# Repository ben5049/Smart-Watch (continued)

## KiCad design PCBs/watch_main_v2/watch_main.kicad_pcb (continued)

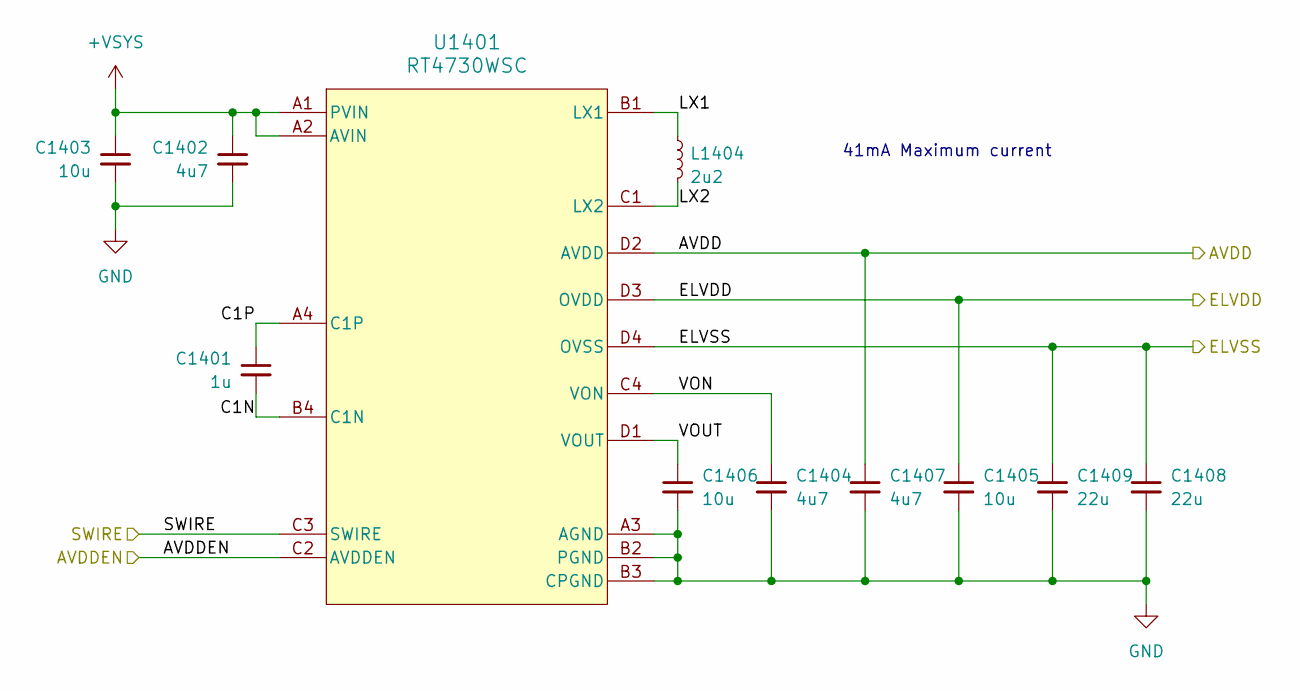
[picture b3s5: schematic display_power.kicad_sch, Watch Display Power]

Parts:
C1401: 1u; C_0402_1005Metric
C1402, C1404, C1407: 4u7; C_0402_1005Metric
C1403, C1405, C1406: 10u; C_0402_1005Metric
C1408, C1409: 22u; C_0402_1005Metric
L1404: 2u2; L_Murata_DFE201610P
U1401: RT4730WSC

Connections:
+VSYS: C1402.1, C1403.1, U1401.A1 (PVIN), U1401.A2 (AVIN); also elsewhere on the board
/Display Connector/AVDD: C1407.1, U1401.D2 (AVDD); also elsewhere on the board
/Display Connector/ELVDD: C1405.1, U1401.D3 (OVDD); also elsewhere on the board
/Display Connector/SWIRE: U1401.C3 (SWIRE); also elsewhere on the board
/Display Power/AVDDEN: U1401.C2 (AVDDEN); also elsewhere on the board
/Display Power/C1N: C1401.2, U1401.B4 (C1N)
/Display Power/C1P: C1401.1, U1401.A4 (C1P)
/Display Power/ELVSS: C1408.1, C1409.1, U1401.D4 (OVSS); also elsewhere on the board
/Display Power/LX1: L1404.1, U1401.B1 (LX1)
/Display Power/LX2: L1404.2, U1401.C1 (LX2)
/Display Power/VON: C1404.1, U1401.C4 (VON)
/Display Power/VOUT: C1406.1, U1401.D1 (VOUT)
GND: C1402.2, C1403.2, C1404.2, C1405.2, C1406.2, C1407.2, C1408.2, C1409.2, U1401.A3 (AGND), U1401.B2 (PGND), U1401.B3 (CPGND); also elsewhere on the board

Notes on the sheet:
41mA Maximum current

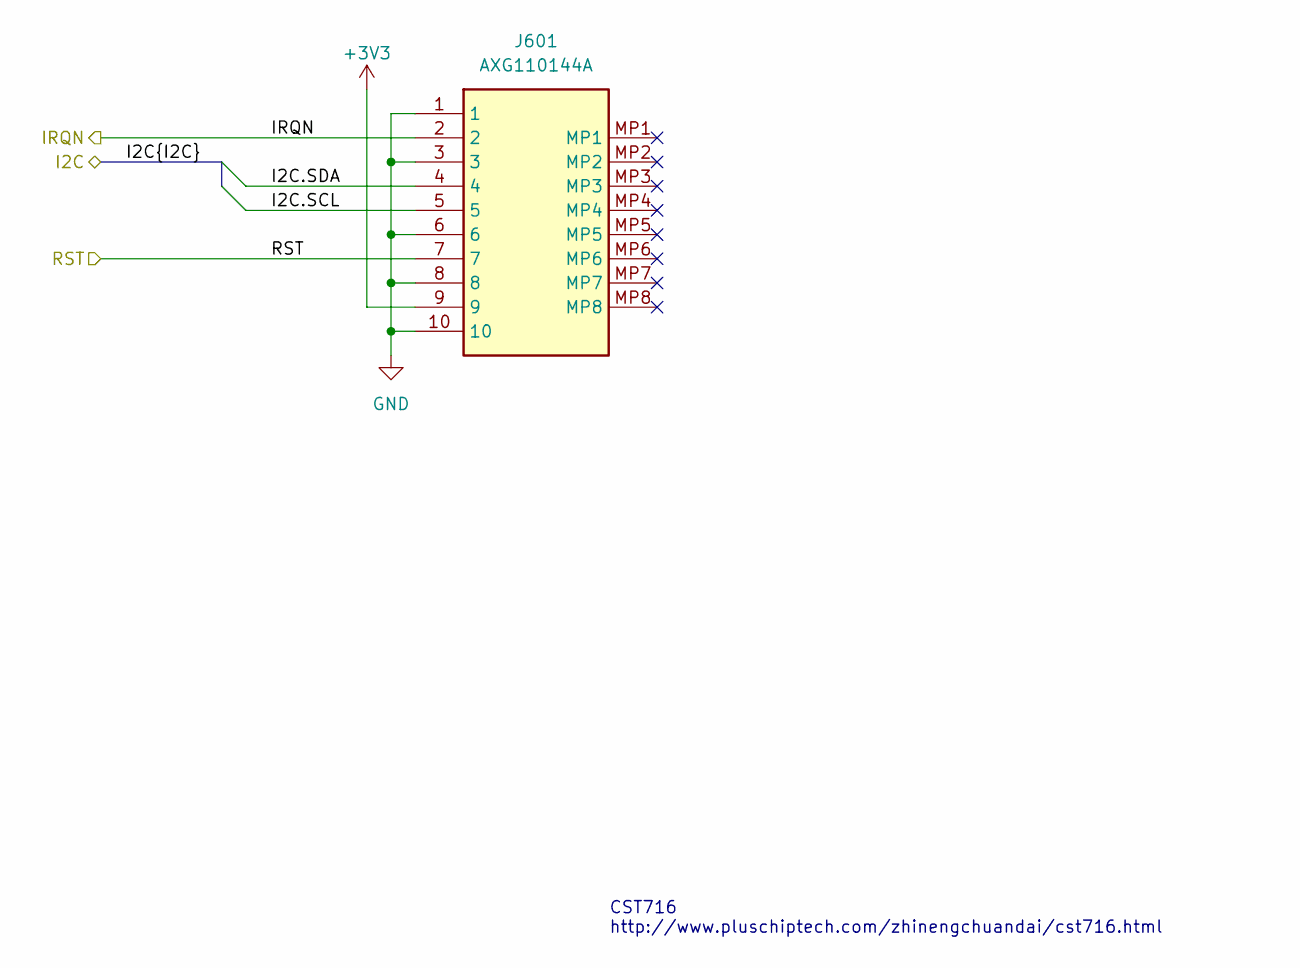
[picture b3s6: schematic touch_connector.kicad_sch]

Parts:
J601: AXG110144A; Mouser Part Number N/A

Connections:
+3V3: J601.9; also elsewhere on the board
/I2C1.SCL: J601.5; also elsewhere on the board
/I2C1.SDA: J601.4; also elsewhere on the board
/STM32/TOUCH_INT: J601.2; also elsewhere on the board
/STM32/TOUCH_RST: J601.7; also elsewhere on the board
GND: J601.1, J601.3, J601.6, J601.8, J601.10; also elsewhere on the board

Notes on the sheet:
CST716 http://www.pluschiptech.com/zhinengchuandai/cst716.html

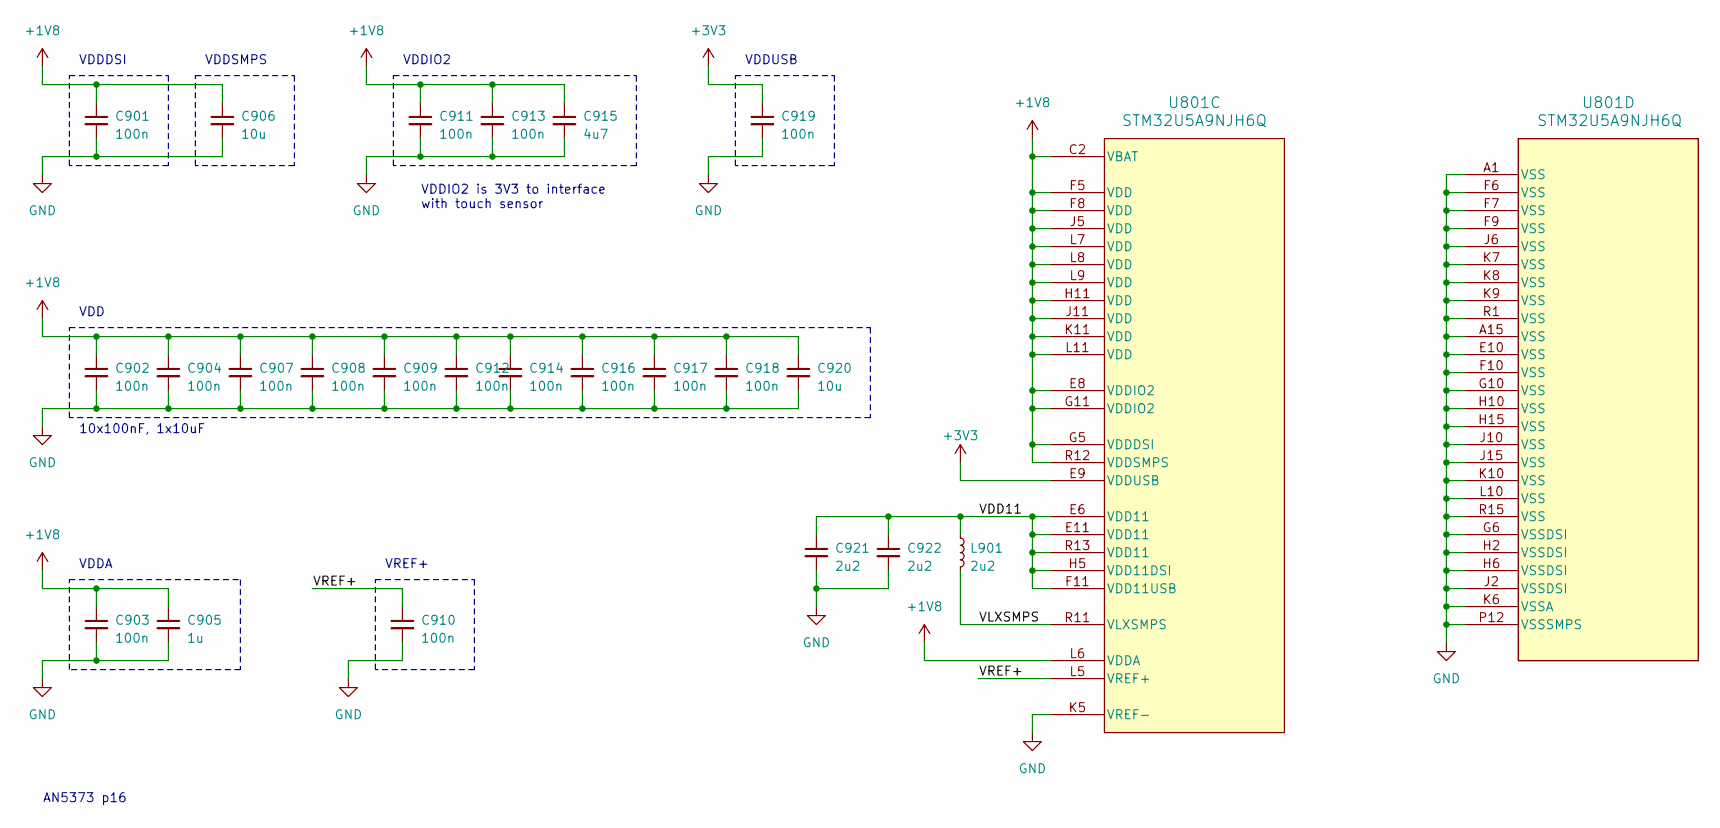
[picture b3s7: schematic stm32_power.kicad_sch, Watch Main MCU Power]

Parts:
C901, C902, C903, C904, C907, C908, C909, C910, C911, C912, C913, C914, C916, C917, C918, C919: 100n; C_0402_1005Metric
C905: 1u; C_0402_1005Metric
C906, C920: 10u; C_0402_1005Metric
C915: 4u7; C_0402_1005Metric
C921, C922: 2u2; C_0402_1005Metric
L901: 2u2; L_Murata_DFE201610P
U801: STM32U5A9NJH6Q; TFBGA216_13X13_STM

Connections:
+1V8: C901.1, C902.1, C903.1, C904.1, C905.1, C906.1, C907.1, C908.1, C909.1, C911.1, C912.1, C913.1, C914.1, C915.1, C916.1, C917.1, C918.1, C920.1, U801.C2 (VBAT), U801.E8 (VDDIO2), U801.F5 (VDD), U801.F8 (VDD), U801.G5 (VDDDSI), U801.G11 (VDDIO2), U801.H11 (VDD), U801.J5 (VDD), U801.J11 (VDD), U801.K11 (VDD), U801.L6 (VDDA), U801.L7 (VDD), U801.L8 (VDD), U801.L9 (VDD), U801.L11 (VDD), U801.R12 (VDDSMPS); also elsewhere on the board
+3V3: C919.1, U801.E9 (VDDUSB); also elsewhere on the board
/STM32 Power/VDD11: C921.1, C922.1, L901.1, U801.E6 (VDD11), U801.E11 (VDD11), U801.F11 (VDD11USB), U801.H5 (VDD11DSI), U801.R13 (VDD11)
/STM32 Power/VLXSMPS: L901.2, U801.R11 (VLXSMPS)
/STM32 Power/VREF+: C910.1, U801.L5 (VREF+)
GND: C901.2, C902.2, C903.2, C904.2, C905.2, C906.2, C907.2, C908.2, C909.2, C910.2, C911.2, C912.2, C913.2, C914.2, C915.2, C916.2, C917.2, C918.2, C919.2, C920.2, C921.2, C922.2, U801.A1 (VSS), U801.A15 (VSS), U801.E10 (VSS), U801.F6 (VSS), U801.F7 (VSS), U801.F9 (VSS), U801.F10 (VSS), U801.G6 (VSSDSI), U801.G10 (VSS), U801.H2 (VSSDSI), U801.H6 (VSSDSI), U801.H10 (VSS), U801.H15 (VSS), U801.J2 (VSSDSI), U801.J6 (VSS), U801.J10 (VSS), U801.J15 (VSS), U801.K5 (VREF-), U801.K6 (VSSA), U801.K7 (VSS), U801.K8 (VSS), U801.K9 (VSS), U801.K10 (VSS), U801.L10 (VSS), U801.P12 (VSSSMPS), U801.R1 (VSS), U801.R15 (VSS); also elsewhere on the board

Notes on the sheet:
VDDIO2 is 3V3 to interface with touch sensor
VDDUSB
VDDIO2
VREF+
VDD
VDDSMPS
VDDA
AN5373 p16
10x100nF, 1x10uF
VDDDSI

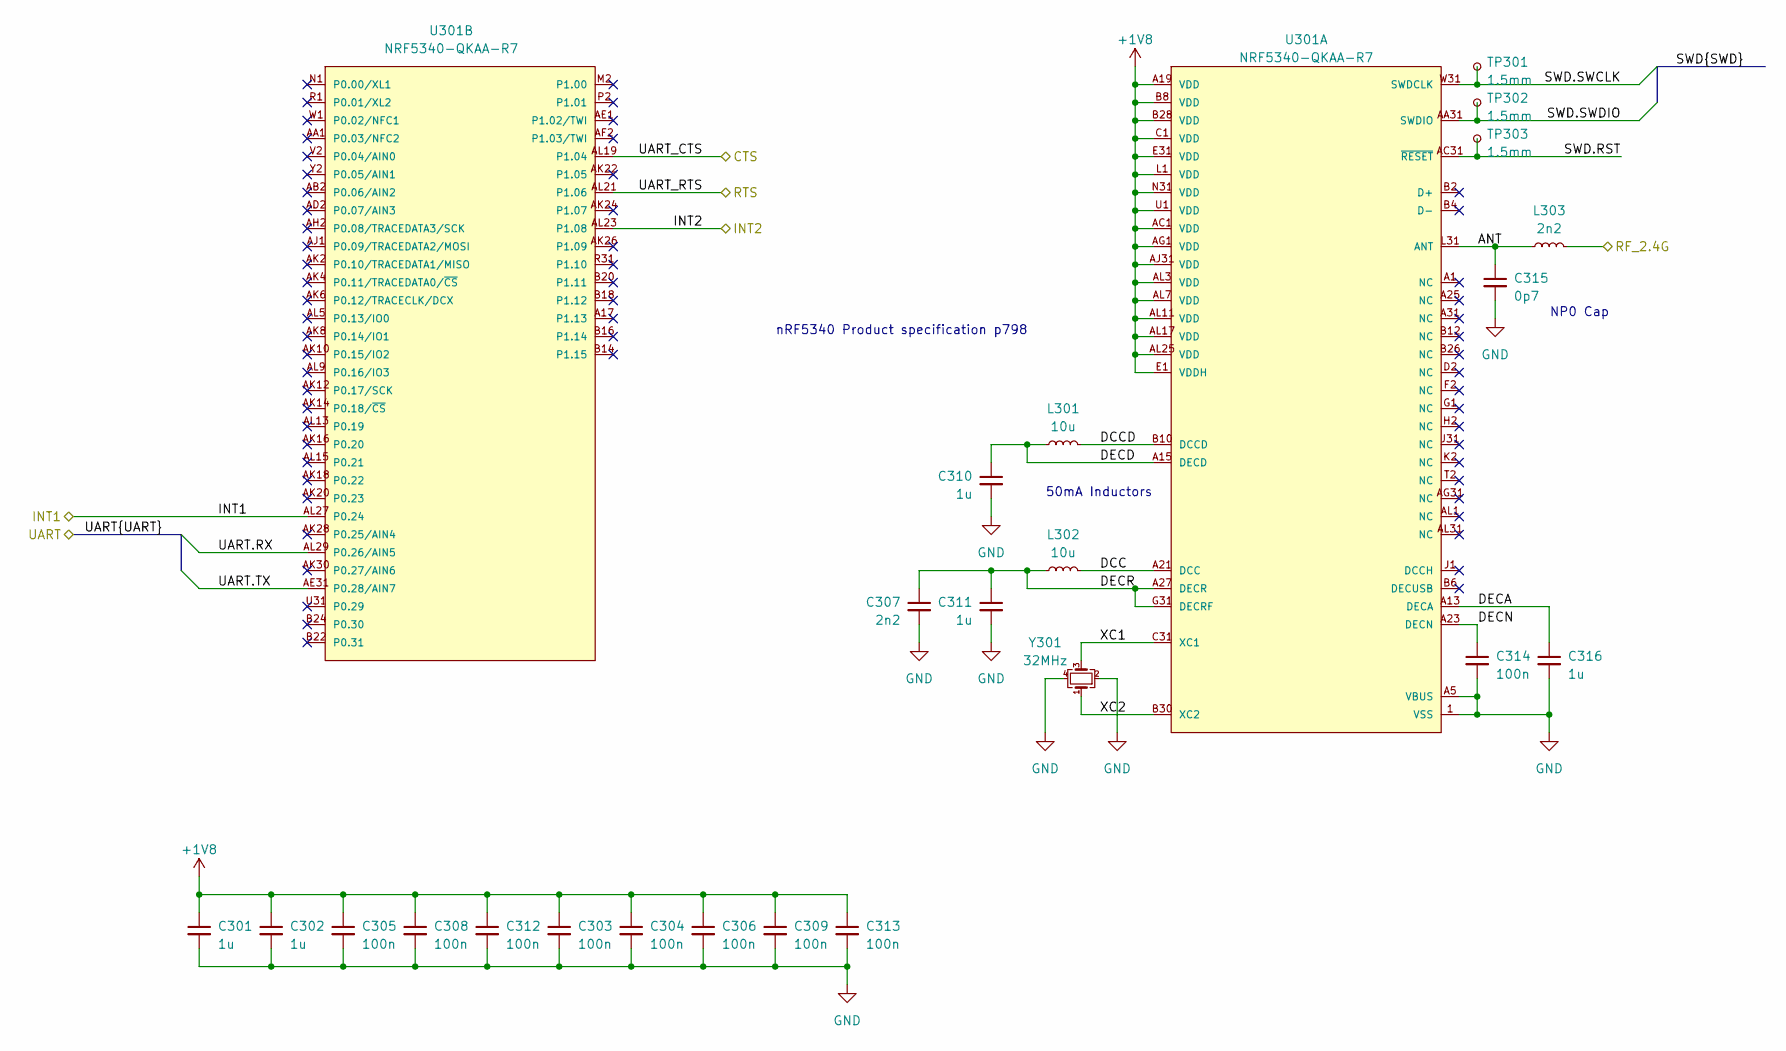
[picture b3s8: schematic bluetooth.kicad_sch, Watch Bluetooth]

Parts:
C301, C302, C310, C311, C316: 1u; C_0402_1005Metric
C303, C304, C305, C306, C308, C309, C312, C313, C314: 100n; C_0402_1005Metric
C307: 2n2; C_0402_1005Metric
C315: 0p7; C_0402_1005Metric
L301, L302: 10u; L_TDK_MLZ1608
L303: 2n2; L_0402_1005Metric
TP301, TP302, TP303: 1.5mm; TestPoint_Pad_D1.5mm
U301: NRF5340-QKAA-R7; NRF5340-QKAA-R7_modified; mouser part number 949-NRF5340-QKAA-R7; digikey description BLE 5.2 SOC
Y301: 32MHz; Crystal_SMD_2016-4Pin_2.0x1.6mm

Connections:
+1V8: C301.1, C302.1, C303.1, C304.1, C305.1, C306.1, C308.1, C309.1, C312.1, C313.1, U301.A19 (VDD), U301.AC1 (VDD), U301.AG1 (VDD), U301.AJ31 (VDD), U301.AL3 (VDD), U301.AL7 (VDD), U301.AL11 (VDD), U301.AL17 (VDD), U301.AL25 (VDD), U301.B8 (VDD), U301.B28 (VDD), U301.C1 (VDD), U301.E1 (VDDH), U301.E31 (VDD), U301.L1 (VDD), U301.N31 (VDD), U301.U1 (VDD); also elsewhere on the board
/Antenna/RF_2.4G: L303.2; also elsewhere on the board
/Bluetooth/ANT: C315.1, L303.1, U301.L31 (ANT)
/Bluetooth/DCC: L302.2, U301.A21 (DCC)
/Bluetooth/DCCD: L301.2, U301.B10 (DCCD)
/Bluetooth/DECA: C316.1, U301.A13 (DECA)
/Bluetooth/DECD: C310.1, L301.1, U301.A15 (DECD)
/Bluetooth/DECN: C314.1, U301.A23 (DECN)
/Bluetooth/DECR: C307.1, C311.1, L302.1, U301.A27 (DECR), U301.G31 (DECRF)
/Bluetooth/INT1: U301.AL27 (P0.24); also elsewhere on the board
/Bluetooth/INT2: U301.AL23 (P1.08); also elsewhere on the board
/Bluetooth/SWD.RST: TP303.1, U301.AC31 (~RESET)
/Bluetooth/SWD.SWCLK: TP301.1, U301.W31 (SWDCLK)
/Bluetooth/SWD.SWDIO: TP302.1, U301.AA31 (SWDIO)
/Bluetooth/UART_CTS: U301.AL19 (P1.04); also elsewhere on the board
/Bluetooth/UART_RTS: U301.AL21 (P1.06); also elsewhere on the board
/Bluetooth/XC1: U301.C31 (XC1), Y301.3
/Bluetooth/XC2: U301.B30 (XC2), Y301.1
/LPUART1.RX: U301.AL29 (P0.26/AIN5); also elsewhere on the board
/LPUART1.TX: U301.AE31 (P0.28/AIN7); also elsewhere on the board
GND: C301.2, C302.2, C303.2, C304.2, C305.2, C306.2, C307.2, C308.2, C309.2, C310.2, C311.2, C312.2, C313.2, C314.2, C315.2, C316.2, U301.1 (VSS), U301.A5 (VBUS), Y301.2, Y301.4; also elsewhere on the board

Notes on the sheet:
nRF5340 Product specification p798
NP0 Cap
50mA Inductors

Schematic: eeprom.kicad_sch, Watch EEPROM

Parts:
IC1801: M24256X-FCU6T_VF; BGA4C50P2X2_70X98X33; Mouser Part Number 511-M24256X-FCU6T/VF

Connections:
+1V8: IC1801.A1 (VCC); also elsewhere on the board
/I2C4.SCL: IC1801.A2 (SCL); also elsewhere on the board
/I2C4.SDA: IC1801.B1 (SDA); also elsewhere on the board
GND: IC1801.B2 (VSS); also elsewhere on the board

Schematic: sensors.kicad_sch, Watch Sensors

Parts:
C1301: 220n; C_0402_1005Metric
C1302, C1304, C1305, C1306, C1307: 100n; C_0402_1005Metric
C1303: 10u; C_0402_1005Metric
IC1301: IIS2MDCTR; Mouser Part Number 511-IIS2MDCTR
IC1302: OPT3004DNPR; SON65P200X200X65-7N-D; Mouser Part Number 595-OPT3004DNPR
U1301: LSM6DSO16IS; LGA14_LSM6_STM

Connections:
+1V8: C1302.1, C1303.1, C1304.1, C1305.1, C1306.1, C1307.1, IC1301.9 (VDD), IC1301.10 (VDD_IO), IC1302.1 (VDD), U1301.2 (MSDA), U1301.3 (MSCL), U1301.5 (VDD_IO), U1301.8 (VDD); also elsewhere on the board
/I2C3.SCL: IC1301.1 (SCL/SPC), IC1302.4 (SCL); also elsewhere on the board
/I2C3.SDA: IC1301.4 (SDA/SDI/SDO), IC1302.6 (SDA); also elsewhere on the board
/SPI1.CS: U1301.12 (CS); also elsewhere on the board
/SPI1.MISO: U1301.1 (SDO/SA0); also elsewhere on the board
/SPI1.MOSI: U1301.14 (SDA); also elsewhere on the board
/SPI1.SCK: U1301.13 (SCL); also elsewhere on the board
/STM32/ALS_INT: IC1302.5 (INT); also elsewhere on the board
/STM32/IMU_INT1: U1301.4 (INT1); also elsewhere on the board
/STM32/IMU_INT2: U1301.9 (INT2); also elsewhere on the board
/STM32/MAG_INT: IC1301.7 (INT/DRDY); also elsewhere on the board
/Sensors/C1: C1301.1, IC1301.5 (C1)
GND: C1301.2, C1302.2, C1303.2, C1304.2, C1305.2, C1306.2, C1307.2, IC1301.6 (GND_1), IC1301.8 (GND_2), IC1302.2 (ADDR), IC1302.3 (GND), IC1302.7 (EP), U1301.6 (GND), U1301.7 (GND); also elsewhere on the board

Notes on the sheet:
Address = 0x1E
Address = 0x6A (SA0=0)
Address = 0x44 (ADDR=0)
Typical application: LSM6DSO16IS datasheet p25
Typical application: IIS2MDCTR datasheet p19
Typical application: OPT3004 datasheet p19

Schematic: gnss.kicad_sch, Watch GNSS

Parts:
C401: 10n; C_0402_1005Metric
C402: 120p; C_0402_1005Metric
C403: 100n; C_0402_1005Metric
FL401: B39162B4327P810; mouser part number 871-B39162B4327P810; digikey description FILTER SAW 5SMD
IC401: BGA725L6E6327FTSA1; BGS12SN6E6327XTSA1; Mouser Part Number 726-BGA725L6E6327FTS
L401: 7n5; L_0402_1005Metric
R401: 10k; R_0402_1005Metric
U401: TESEO-LIV3FL; TESEOLIV3FL; Mouser Part Number 511-TESEO-LIV4FTR

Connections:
+1V8: C403.1, U401.6 (VBAT), U401.7 (VCCIO), U401.8 (VCC); also elsewhere on the board
/GNSS/ANT_OFF: IC401.6 (PON), R401.1, U401.13 (ANT_OFF)
/GNSS/LNA_IN: IC401.5 (AI), L401.2
/GNSS/LNA_OUT: FL401.1 (IN), IC401.3 (AO)
/GNSS/PPS: U401.4 (PPS); also elsewhere on the board
/GNSS/RF_1.575G: L401.1; also elsewhere on the board
/GNSS/RF_IN: C402.2, U401.11 (RF_IN)
/GNSS/RST: U401.9 (NRESET); also elsewhere on the board
/GNSS/SAW_OUT: C402.1, FL401.4 (OUT)
/GNSS/VCC_RF: C401.1, IC401.2 (VCC), U401.14 (VCC_RF)
/GNSS/WAKEUP: U401.5 (WAKEUP); also elsewhere on the board
/USART1.RX: U401.2 (UART-TX); also elsewhere on the board
/USART1.TX: U401.3 (UART-RX); also elsewhere on the board
GND: C401.2, C403.2, FL401.2 (GND_1), FL401.3 (GND_2), FL401.5 (GND_3), IC401.1 (GND), IC401.4 (GNDRF), R401.2, U401.1 (GND), U401.10 (GND_RF_1), U401.12 (GND_RF_2); also elsewhere on the board

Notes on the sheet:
UM2980 p12

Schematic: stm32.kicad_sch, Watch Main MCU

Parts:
C801, C802, C803, C804: 6p; C_0402_1005Metric
R801, R802, R803, R804, R805, R806, R807, R808, R809, R810: 4k7; R_0402_1005Metric
TP801, TP804, TP805, TP806, TP807: 1.5mm; TestPoint_Pad_D1.5mm
U801: STM32U5A9NJH6Q; TFBGA216_13X13_STM
Y801: 16MHz; Crystal_SMD_2016-4Pin_2.0x1.6mm
Y802: 32.768kHz; Crystal_SMD_2012-2Pin_2.0x1.2mm

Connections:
+1V8: R801.1, R802.1, R803.1, R804.1, R805.1, R806.1, R809.1, R810.1; also elsewhere on the board
+3V3: R807.1, R808.1; also elsewhere on the board
/Bluetooth/INT1: U801.C15 (PC6); also elsewhere on the board
/Bluetooth/INT2: U801.B15 (PC7); also elsewhere on the board
/Bluetooth/UART_CTS: U801.M6 (PB1); also elsewhere on the board
/Bluetooth/UART_RTS: U801.E14 (PG5); also elsewhere on the board
/DSI.CKN: U801.J1 (DSI_CKN); also elsewhere on the board
/DSI.CKP: U801.H1 (DSI_CKP); also elsewhere on the board
/DSI.D0N: U801.G2 (DSI_D0N); also elsewhere on the board
/DSI.D0P: U801.G1 (DSI_D0P); also elsewhere on the board
/Display Connector/DSI_TE: U801.L1 (PF10); also elsewhere on the board
/Display Connector/RESET: U801.L3 (PF7); also elsewhere on the board
/Display Connector/SWIRE: U801.A6 (PG12), U801.B7 (PG10); also elsewhere on the board
/Display Connector/TP_INT: U801.F2 (PJ8); also elsewhere on the board
/Display Connector/TP_RST: U801.E1 (PJ7); also elsewhere on the board
/Display Power/AVDDEN: U801.A7 (PG9); also elsewhere on the board
/Expansion Connector/GPIO1: U801.D9 (PD0); also elsewhere on the board
/Expansion Connector/GPIO2: U801.C9 (PD1); also elsewhere on the board
/Flash/CS2: U801.N4 (PA0); also elsewhere on the board
/Flash/INT: U801.F15 (PI13); also elsewhere on the board
/Flash/RST: U801.F14 (PI14); also elsewhere on the board
/Flash/RSTO: U801.G15 (PI10); also elsewhere on the board
/GNSS/PPS: U801.D12 (PA10); also elsewhere on the board
/GNSS/RST: U801.D1 (PJ3); also elsewhere on the board
/GNSS/WAKEUP: U801.E2 (PJ6); also elsewhere on the board
/I2C1.SCL: R807.2, U801.D7 (PG14); also elsewhere on the board
/I2C1.SDA: R808.2, U801.B6 (PG13); also elsewhere on the board
/I2C2.SCL: R801.2, U801.M12 (PB13); also elsewhere on the board
/I2C2.SDA: R802.2, U801.P13 (PB14); also elsewhere on the board
/I2C3.SCL: R803.2, U801.P2 (PC0); also elsewhere on the board
/I2C3.SDA: R804.2, U801.M1 (PC1); also elsewhere on the board
/I2C4.SCL: R805.2, U801.M13 (PD12); also elsewhere on the board
/I2C4.SDA: R806.2, U801.N14 (PD13); also elsewhere on the board
/I2C6.SCL: R809.2, U801.F1 (PJ10); also elsewhere on the board
/I2C6.SDA: R810.2, U801.H3 (PF0); also elsewhere on the board
/LPUART1.RX: U801.E13 (PG8); also elsewhere on the board
/LPUART1.TX: U801.D13 (PG7); also elsewhere on the board
/Micro SD/CD: U801.A9 (PD3); also elsewhere on the board
/Micro SD/EN: U801.A8 (PD4); also elsewhere on the board
/Microphone/CLOCK: U801.P9 (PE9); also elsewhere on the board
/Microphone/DATA: U801.P10 (PE10); also elsewhere on the board
/OSPI1.CLKN: U801.M11 (PB12); also elsewhere on the board
/OSPI1.CLKP: U801.N12 (PB10); also elsewhere on the board
/OSPI1.CS: U801.P11 (PE11); also elsewhere on the board
/OSPI1.DQS: U801.D14 (PG6); also elsewhere on the board
/OSPI1.IO0: U801.J14 (PI3); also elsewhere on the board
/OSPI1.IO1: U801.J13 (PI2); also elsewhere on the board
/OSPI1.IO2: U801.J12 (PI1); also elsewhere on the board
/OSPI1.IO3: U801.D10 (PH8); also elsewhere on the board
/OSPI1.IO4: U801.M14 (PH9); also elsewhere on the board
/OSPI1.IO5: U801.L13 (PH10); also elsewhere on the board
/OSPI1.IO6: U801.L14 (PH11); also elsewhere on the board
/OSPI1.IO7: U801.M15 (PH12); also elsewhere on the board
/Power/ENCHG: U801.R14 (PB15); also elsewhere on the board
/Power/INT: U801.P14 (PD10); also elsewhere on the board
/SDMMC1.CK: U801.C10 (PC12); also elsewhere on the board
/SDMMC1.CKIN: U801.C6 (PB8); also elsewhere on the board
/SDMMC1.CMD: U801.B9 (PD2); also elsewhere on the board
/SDMMC1.D0: U801.A14 (PC8); also elsewhere on the board
/SDMMC1.D1: U801.C14 (PC9); also elsewhere on the board
/SDMMC1.D2: U801.A10 (PC10); also elsewhere on the board
/SDMMC1.D3: U801.B10 (PC11); also elsewhere on the board
/SPI1.CS: U801.N6 (PB0); also elsewhere on the board
/SPI1.MISO: U801.P5 (PA6); also elsewhere on the board
/SPI1.MOSI: U801.R5 (PA7); also elsewhere on the board
/SPI1.SCK: U801.R4 (PA5); also elsewhere on the board
/STM32/ALS_INT: U801.M2 (PF6); also elsewhere on the board
/STM32/BTN: U801.M8 (PE8); also elsewhere on the board
/STM32/GPIO3: TP801.1, U801.B5
/STM32/HR_INT: U801.N15 (PD14); also elsewhere on the board
/STM32/IMU_INT1: U801.R7 (PB2); also elsewhere on the board
/STM32/IMU_INT2: U801.R8 (PF14); also elsewhere on the board
/STM32/LRA_EN: U801.P15 (PD9); also elsewhere on the board
/STM32/MAG_INT: U801.R6 (PC4); also elsewhere on the board
/STM32/OSC32_IN: C803.2, U801.B1 (PC14-OSC32_IN), Y802.2
/STM32/OSC32_OUT: C804.2, U801.C1 (PC15-OSC32_OUT), Y802.1
/STM32/OSC_IN: C801.2, U801.N1 (PH0-OSC_IN), Y801.3
/STM32/OSC_OUT: C802.2, U801.N2 (PH1-OSC_OUT), Y801.1
/STM32/SWD.RST: TP807.1, U801.R2 (NRST)
/STM32/SWD.SWCLK: TP806.1, U801.A12 (PA14)
/STM32/SWD.SWDIO: TP805.1, U801.C13 (PA13)
/STM32/SWO: TP804.1, U801.E7 (PB3)
/STM32/TOUCH_INT: U801.N9 (PE7); also elsewhere on the board
/STM32/TOUCH_RST: U801.N11 (PE12); also elsewhere on the board
/USART1.RX: U801.A3 (PB7); also elsewhere on the board
/USART1.TX: U801.A4 (PB6); also elsewhere on the board
/USART6.RX: U801.P1 (PC2); also elsewhere on the board
/USART6.TX: U801.N3 (PC3); also elsewhere on the board
/USB.DN: U801.B14 (PA11); also elsewhere on the board
/USB.DP: U801.B13 (PA12); also elsewhere on the board
GND: C801.1, C802.1, C803.1, C804.1, U801.B4 (PH3-BOOT0), Y801.2, Y801.4; also elsewhere on the board

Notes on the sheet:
CL = 8pF CS = 5pF ∴ CLx = 6pF
CL = 7pF CS = 4pF ∴ CLx = 6pF

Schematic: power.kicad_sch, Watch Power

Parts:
C201: 2u2; C_0402_1005Metric
C202: 1u; C_0402_1005Metric
C203, C204, C205, C206, C207, C208: 10u; C_0402_1005Metric
IC201: ADP5360ACBZ-2-R7; ADP5360ACBZ1R7; Mouser Part Number 584-ADP5360ACBZ-2-R7
L201, L202: 4u7; L_Murata_DFE201610P
Q201: DMP2104LP-7; DMP2104LP7; Mouser Part Number 621-DMP2104LP-7
R201: 10k; R_0402_1005Metric
R202: 100k; R_0402_1005Metric
TP201, TP202, TP208, TP209: 1.5mm; TestPoint_Pad_D1.5mm

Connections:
+1V8: C206.1, IC201.D1 (FB1), L201.2; also elsewhere on the board
+3V3: C207.1, IC201.A3 (VOUT2); also elsewhere on the board
+VBAT: C203.1, IC201.C6 (BSNS), IC201.D6 (ISOB), TP202.1; also elsewhere on the board
+VSYS: C204.1, C205.1, C208.1, IC201.C1 (VIN2), IC201.D2 (VID1), IC201.E2 (EN1), IC201.E6 (VSYS), IC201.F2 (VIN1); also elsewhere on the board
/I2C2.SCL: IC201.A4 (SCL); also elsewhere on the board
/I2C2.SDA: IC201.A5 (SDA); also elsewhere on the board
/Power/ENCHG: IC201.F3 (ENCHG); also elsewhere on the board
/Power/INT: IC201.A6 (~INT); also elsewhere on the board
/Power/SWA_3V3: IC201.B1 (SW2A), L202.1
/Power/SWB_3V3: IC201.A2 (SW2B), L202.2
/Power/SW_1V8: IC201.E1 (SW1), L201.1
/Power/THR: IC201.B6 (THR), R202.1
/Power/VBUS_PROTECTED: C201.1, IC201.F6 (VBUS), Q201.3 (S)
/STM32/BTN: IC201.E4 (~MR), R201.2; also elsewhere on the board
GND: C201.2, C202.2, C203.2, C204.2, C205.2, C206.2, C207.2, C208.2, IC201.A1 (PGND2), IC201.B2 (AGND2), IC201.B3 (ENSD), IC201.B4 (EN2), IC201.F1 (PGND1), IC201.F4 (AGND1), Q201.1 (G), R202.2, TP201.1, TP208.1, TP209.1; also elsewhere on the board
VBUS: Q201.2 (D); also elsewhere on the board
VDD: C202.1, IC201.F5 (VDD), R201.1

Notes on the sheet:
VID1 = VIN1 ∴ VOUT1 = 1V8 (ADP5360ACBZ-2-R7 p59)
INT needs to be pulled up by host
I2C Address: 0x46
I2C Pullups on STM32 sheet

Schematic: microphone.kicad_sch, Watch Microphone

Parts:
C1801: 100n; C_0402_1005Metric
MIC1801: IM70D122V01XTMA1; PG-TLGA-5-2_INF

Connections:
+1V8: C1801.1, MIC1801.1 (VDD); also elsewhere on the board
/Microphone/CLOCK: MIC1801.2 (CLOCK); also elsewhere on the board
/Microphone/DATA: MIC1801.3 (DATA); also elsewhere on the board
GND: C1801.2, MIC1801.4 (LR_SELECT), MIC1801.5 (GND); also elsewhere on the board

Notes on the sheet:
PDM Interface

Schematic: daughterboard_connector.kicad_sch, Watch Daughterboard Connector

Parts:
J701: AXG120144; Manufacturer_Part_Number AXG120144; Mouser Part Number 769-AXG120144

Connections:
+1V8: J701.2, J701.19; also elsewhere on the board
+3V3: J701.1, J701.20; also elsewhere on the board
+VBAT: J701.6, J701.15; also elsewhere on the board
/I2C4.SCL: J701.9; also elsewhere on the board
/I2C4.SDA: J701.11; also elsewhere on the board
/STM32/HR_INT: J701.12; also elsewhere on the board
/STM32/LRA_EN: J701.10; also elsewhere on the board
GND: J701.3, J701.4, J701.7, J701.8, J701.13, J701.14, J701.17, J701.18; also elsewhere on the board
VBUS: J701.5, J701.16; also elsewhere on the board

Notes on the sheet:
HR sensors address = 0x57 (1010 111x = AE/AF)
LRA driver address = 0x5A (1011 010x = B4/B5)

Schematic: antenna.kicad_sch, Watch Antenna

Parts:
ANT1601: ANT161575TT-3000A1; ANT161575TT3000A1; Mouser Part Number 810-ANT161575TT-30A1
C1601: 43p; C_0402_1005Metric
C1602: 7p5; C_0402_1005Metric
L1601, L1604: 1n5; L_0402_1005Metric
L1602: 0n6; L_0402_1005Metric
L1603: 2n7; L_0402_1005Metric
R1601: 0R; R_0402_1005Metric
U1601: GPS_&_BT_Antenna_Keepout; GPS & BT Antenna

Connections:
/Antenna/Common: ANT1601.2 (COMMON_RADIATOR_ELECTRODE), R1601.1
/Antenna/Ft_2.4GHz: ANT1601.4 (FEED_POINT_FOR_2.4GHZ/5.5GHZ), C1602.1
/Antenna/Ft_5.5GHz: C1602.2, L1602.1
/Antenna/Ft_GPS: ANT1601.1 (FEED_POINT_FOR_GPS), C1601.2
/Antenna/Mt_2.4GHz: L1602.2, L1603.1, L1604.1
/Antenna/RF_2.4G: L1604.2; also elsewhere on the board
/GNSS/RF_1.575G: C1601.1, L1601.1; also elsewhere on the board
GND: L1601.2, L1603.2, R1601.2; also elsewhere on the board

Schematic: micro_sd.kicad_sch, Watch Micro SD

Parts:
C1101: 10u; C_0402_1005Metric
C1102: 100n; C_0402_1005Metric
IC1101: NVT4858HKZ; Mouser Part Number 771-NVT4858HKZ
J1101: 105162-0001; Mouser Part Number 538-105162-0001
U1102: NCP45525IMNTWG-H; NCP45525IMNTWGH; Mouser Part Number 863-NCP45525IMNTWG-H

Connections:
+1V8: C1102.1, IC1101.15 (VCCA); also elsewhere on the board
+3V3: IC1101.14 (VCCB), U1102.1 (VIN), U1102.3 (VCC); also elsewhere on the board
/Micro SD/+3V3_SD: C1101.1, J1101.4 (VDD), U1102.5 (BLEED), U1102.7 (VOUT_1), U1102.8 (VOUT_2)
/Micro SD/CD: J1101.9 (DET); also elsewhere on the board
/Micro SD/CLK: IC1101.8 (CLKB), J1101.5 (CLK)
/Micro SD/CMD: IC1101.13 (CMDB), J1101.3 (CMD)
/Micro SD/DAT0: IC1101.10 (DAT0B), J1101.7 (DAT0)
/Micro SD/DAT1: IC1101.9 (DAT1B), J1101.8 (DAT1)
/Micro SD/DAT2: IC1101.12 (DAT2B), J1101.1 (DAT2)
/Micro SD/DAT3: IC1101.11 (DAT3B), J1101.2 (CD/DAT3)
/Micro SD/EN: U1102.2 (EN); also elsewhere on the board
/SDMMC1.CK: IC1101.5 (CLKA); also elsewhere on the board
/SDMMC1.CKIN: IC1101.6 (CLK_FB); also elsewhere on the board
/SDMMC1.CMD: IC1101.16 (CMDA); also elsewhere on the board
/SDMMC1.D0: IC1101.3 (DAT0A); also elsewhere on the board
/SDMMC1.D1: IC1101.4 (DAT1A); also elsewhere on the board
/SDMMC1.D2: IC1101.1 (DAT2A); also elsewhere on the board
/SDMMC1.D3: IC1101.2 (DAT3A); also elsewhere on the board
GND: C1101.2, C1102.2, IC1101.7 (GND), J1101.6 (VSS), J1101.10 (GND_1), J1101.11 (GND_2), J1101.12 (GND_3), J1101.13 (GND_4), J1101.14 (MP1), J1101.15 (MP2), U1102.4 (GND), U1102.9 (EP); also elsewhere on the board

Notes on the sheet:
CD needs to be pulled up by host
Active high EN

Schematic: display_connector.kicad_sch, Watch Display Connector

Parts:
J501: AXG130144; Mouser Part Number 667-AXG130144

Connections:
+1V8: J501.1, J501.2, J501.5; also elsewhere on the board
/DSI.CKN: J501.28; also elsewhere on the board
/DSI.CKP: J501.27; also elsewhere on the board
/DSI.D0N: J501.25; also elsewhere on the board
/DSI.D0P: J501.24; also elsewhere on the board
/Display Connector/AVDD: J501.3, J501.4; also elsewhere on the board
/Display Connector/DSI_TE: J501.11; also elsewhere on the board
/Display Connector/ELVDD: J501.16, J501.17, J501.18; also elsewhere on the board
/Display Connector/RESET: J501.10; also elsewhere on the board
/Display Connector/SWIRE: J501.12; also elsewhere on the board
/Display Connector/TP_INT: J501.22; also elsewhere on the board
/Display Connector/TP_RST: J501.19; also elsewhere on the board
/Display Power/ELVSS: J501.13, J501.14, J501.15; also elsewhere on the board
/I2C6.SCL: J501.20; also elsewhere on the board
/I2C6.SDA: J501.21; also elsewhere on the board
GND: J501.6, J501.7, J501.8, J501.9, J501.23, J501.26, J501.29; also elsewhere on the board

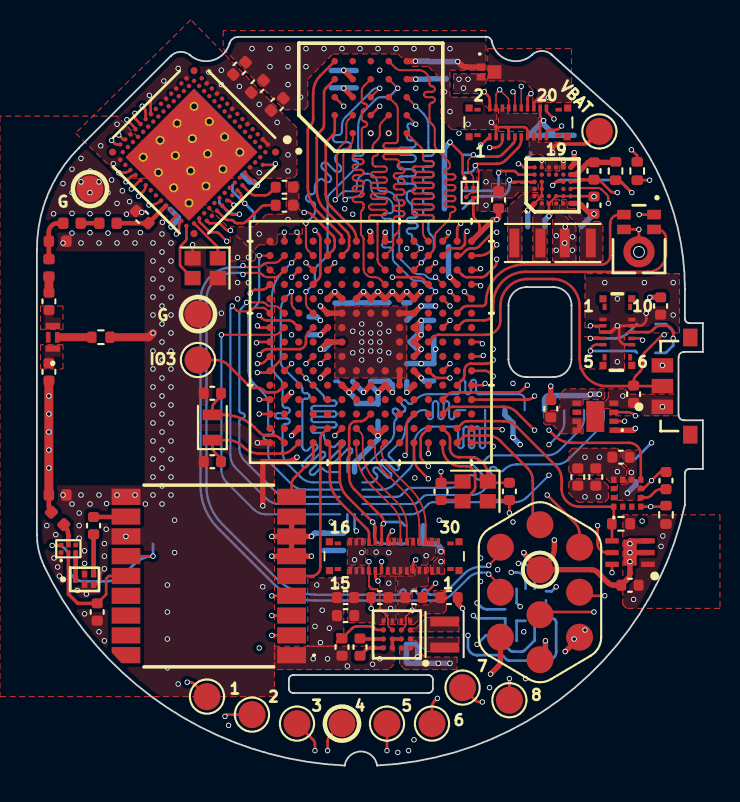
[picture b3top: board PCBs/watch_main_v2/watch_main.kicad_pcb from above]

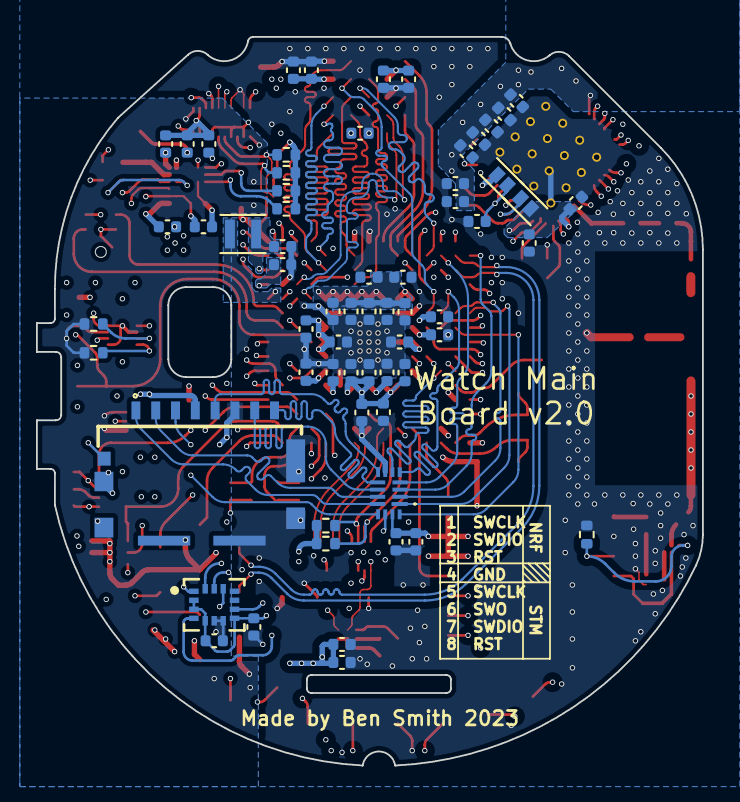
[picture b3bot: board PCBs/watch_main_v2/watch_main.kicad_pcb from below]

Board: 8 copper layers, 37.0 x 40.5 mm, 146 parts (63 on the bottom side), 145 nets.

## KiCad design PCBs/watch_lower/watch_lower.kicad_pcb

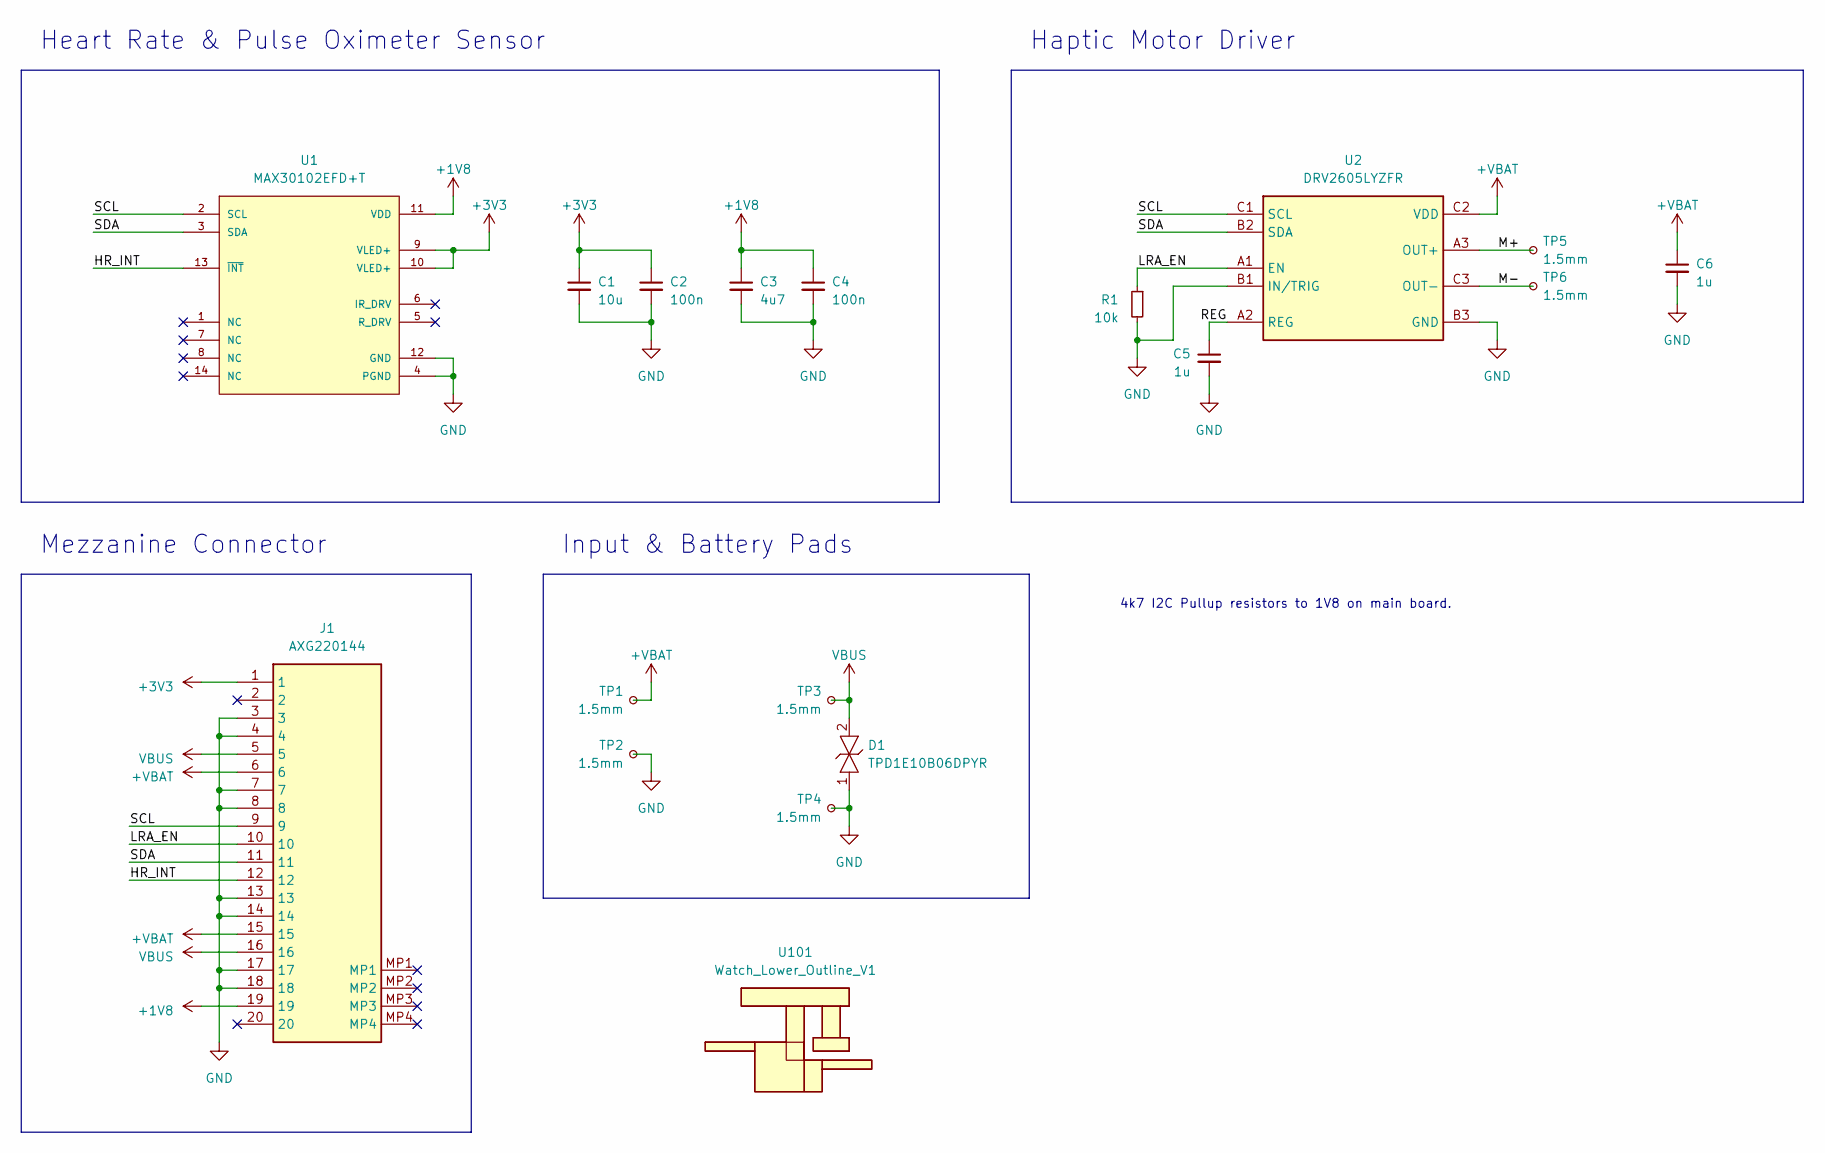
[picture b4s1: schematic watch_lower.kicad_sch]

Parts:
C1: 10u; C_0402_1005Metric
C2, C4: 100n; C_0402_1005Metric
C3: 4u7; C_0402_1005Metric
C5, C6: 1u; C_0402_1005Metric
D1: TPD1E10B06DPYR; Mouser Part Number 595-TPD1E10B06DPYR
J1: AXG220144; Manufacturer_Part_Number AXG220144; Mouser Part Number 769-AXG220144
R1: 10k; R_0402_1005Metric
TP1, TP2, TP3, TP4, TP5, TP6: 1.5mm; TestPoint_Pad_D1.5mm
U1: MAX30102EFD+T; mouser part number 700-MAX30102EFD+T; digikey description INTEGRATED OPTICAL SENSOR
U2: DRV2605LYZFR; BGA9C50P3X3_144X144X62; Mouser Part Number 595-DRV2605LYZFR
U101: Watch_Lower_Outline_V1; Watch Lower Outline V1

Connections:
+1V8: C3.1, C4.1, J1.19, U1.11 (VDD)
+3V3: C1.1, C2.1, J1.1, U1.9 (VLED+), U1.10 (VLED+)
+VBAT: C6.1, J1.6, J1.15, TP1.1, U2.C2 (VDD)
/HR_INT: J1.12, U1.13 (~INT)
/LRA_EN: J1.10, R1.1, U2.A1 (EN)
/M+: TP5.1, U2.A3 (OUT+)
/M-: TP6.1, U2.C3 (OUT-)
/REG: C5.1, U2.A2 (REG)
/SCL: J1.9, U1.2 (SCL), U2.C1 (SCL)
/SDA: J1.11, U1.3 (SDA), U2.B2 (SDA)
GND: C1.2, C2.2, C3.2, C4.2, C5.2, C6.2, D1.1, J1.3, J1.4, J1.7, J1.8, J1.13, J1.14, J1.17, J1.18, R1.2, TP2.1, TP4.1, U1.4 (PGND), U1.12 (GND), U2.B1 (IN/TRIG), U2.B3 (GND)
VBUS: D1.2, J1.5, J1.16, TP3.1

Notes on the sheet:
Mezzanine Connector
Heart Rate & Pulse Oximeter Sensor
Input & Battery Pads
Haptic Motor Driver
4k7 I2C Pullup resistors to 1V8 on main board.

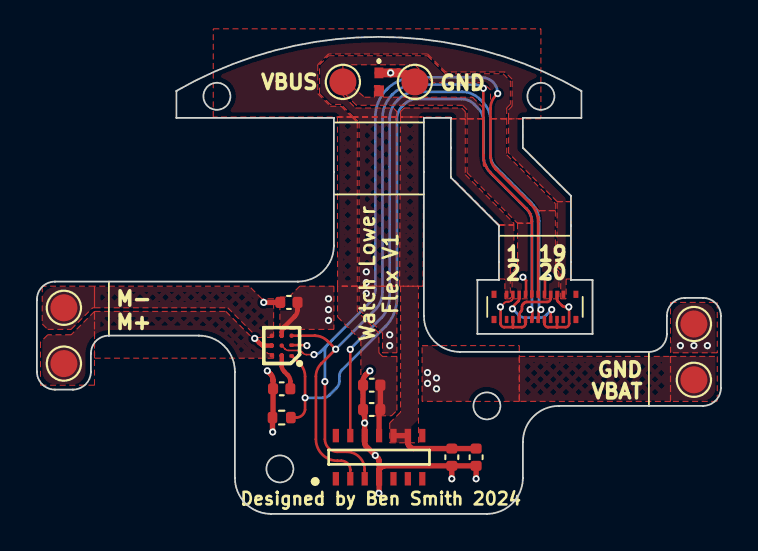
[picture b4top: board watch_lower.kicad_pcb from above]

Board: 2 copper layers, 38.0 x 26.5 mm, 18 parts (0 on the bottom side), 12 nets.
